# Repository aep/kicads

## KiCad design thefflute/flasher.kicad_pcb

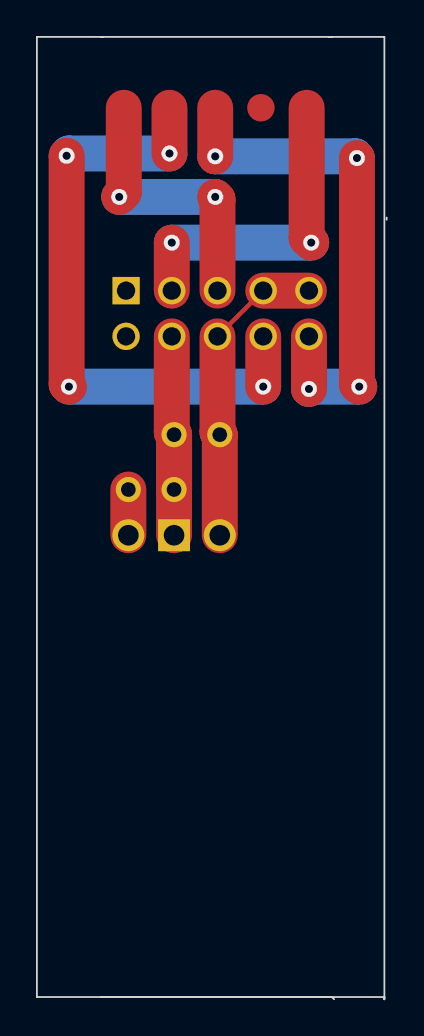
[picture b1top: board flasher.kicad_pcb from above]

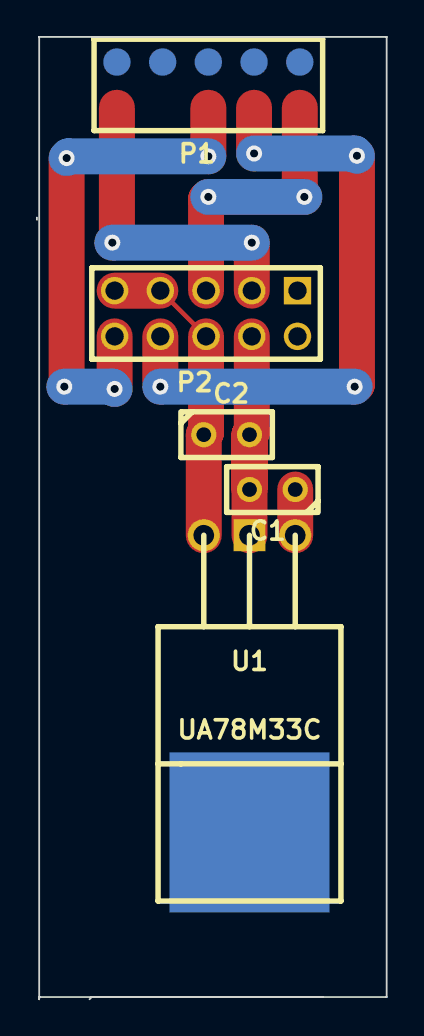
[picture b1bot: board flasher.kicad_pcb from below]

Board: 2 copper layers, 19.4 x 53.5 mm, 5 parts (5 on the bottom side), 7 nets.

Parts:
C1: 33uF; C1
C2: 0.33uF; C1
P1: CONN_5X2; SIDE_MOUNTED_5x2
P2: CONN_5X2; PIN_ARRAY_5x2
U1: UA78M33C; TO220_gnd_in_the_middle

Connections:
unnamed: P1.10, P2.3
unnamed: P1.2, P2.5
unnamed: P1.6, P2.10
unnamed: P1.4, P2.8
unnamed: C1.1, P1.3, U1.1
unnamed: C1.2, C2.2, P1.1, P2.4, U1.2
unnamed: C2.1, P2.6, P2.7, P2.9, U1.3
